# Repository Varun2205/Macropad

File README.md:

# Macropad EAGLE SCHEMATIC
Waveshare RP2040 zero macropad

List of Parts used to make the macropad:

1)Waveshare RP2040 zero ---------- x 1<br>
2)M274 360 Rotatry Encoder ------- x 2<br>
3)Cherry MX Keys/ Gateron Keys --- x 6<br>
4) SMD Diodes (T4 or M7)  -------- x 6<br>

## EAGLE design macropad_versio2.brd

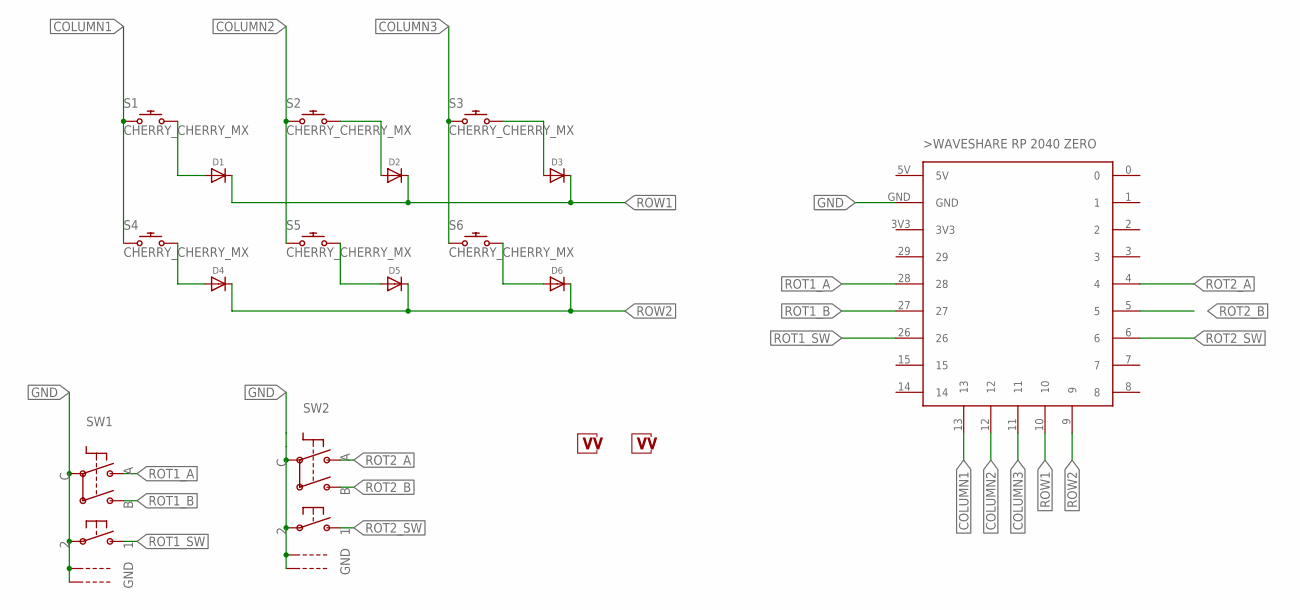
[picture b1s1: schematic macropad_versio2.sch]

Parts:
D1, D2, D3, D4, D5, D6: ADAFRUIT-MACROPAD-2040_MICROBUILDER_DIODESOD-123; ADAFRUIT-MACROPAD-2040_MICROBUILDER_SOD-123
RP2040_ZERO1: WAVESHARE_RP2040_ZERO; WAVESHARE-RP2040-ZERO
S1, S2, S3, S4, S5, S6: CHERRY_CHERRY_MX
SW1, SW2: ADAFRUIT-MACROPAD-2040_ADAFRUIT_ELECTROMECH_ENCOD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; ADAFRUIT-MACROPAD-2040_ADAFRUIT_ELECTROMECH_PEC11+SWITCH
U$1, U$2: LOGO_VV; VV_MEDUIM

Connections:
COLUMN1: RP2040_ZERO1.13, S1.S1 (1), S4.S1 (1)
COLUMN2: RP2040_ZERO1.12, S2.S1 (1), S5.S1 (1)
COLUMN3: RP2040_ZERO1.11, S3.S1 (1), S6.S1 (1)
GND: RP2040_ZERO1.GND, SW1.P$2, SW1.P$C, SW1.P$GND1, SW1.P$GND2, SW2.P$2, SW2.P$C, SW2.P$GND1, SW2.P$GND2
unnamed: D4.A, S4.S2 (2)
unnamed: D5.A, S5.S2 (2)
unnamed: D6.A, S6.S2 (2)
unnamed: D3.A, S3.S2 (2)
unnamed: D2.A, S2.S2 (2)
unnamed: D1.A, S1.S2 (2)
ROT1_A: RP2040_ZERO1.28, SW1.P$A
ROT1_B: RP2040_ZERO1.27, SW1.P$B
ROT1_SW: RP2040_ZERO1.26, SW1.P$1
ROT2_A: RP2040_ZERO1.4, SW2.P$A
ROT2_B: RP2040_ZERO1.5, SW2.P$B
ROT2_SW: RP2040_ZERO1.6, SW2.P$1
ROW1: D1.C, D2.C, D3.C, RP2040_ZERO1.10
ROW2: D4.C, D5.C, D6.C, RP2040_ZERO1.9

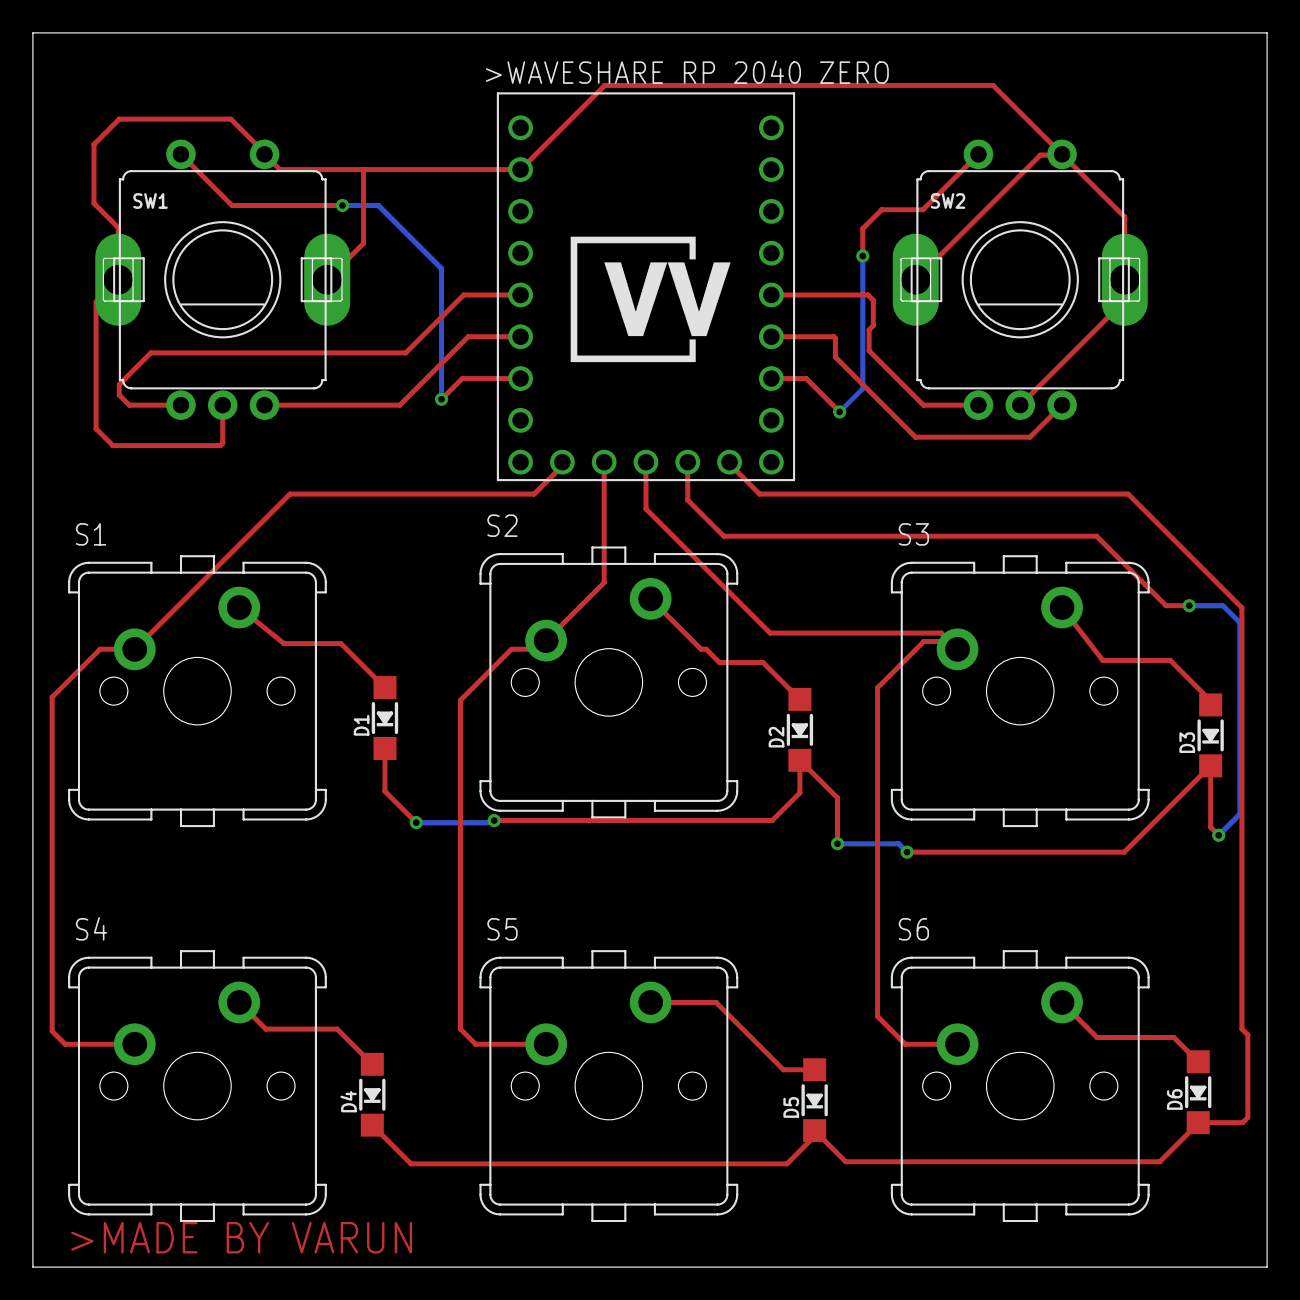
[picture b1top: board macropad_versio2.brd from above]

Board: 2 copper layers, 75.0 x 75.0 mm, 17 parts (1 on the bottom side), 18 nets.
